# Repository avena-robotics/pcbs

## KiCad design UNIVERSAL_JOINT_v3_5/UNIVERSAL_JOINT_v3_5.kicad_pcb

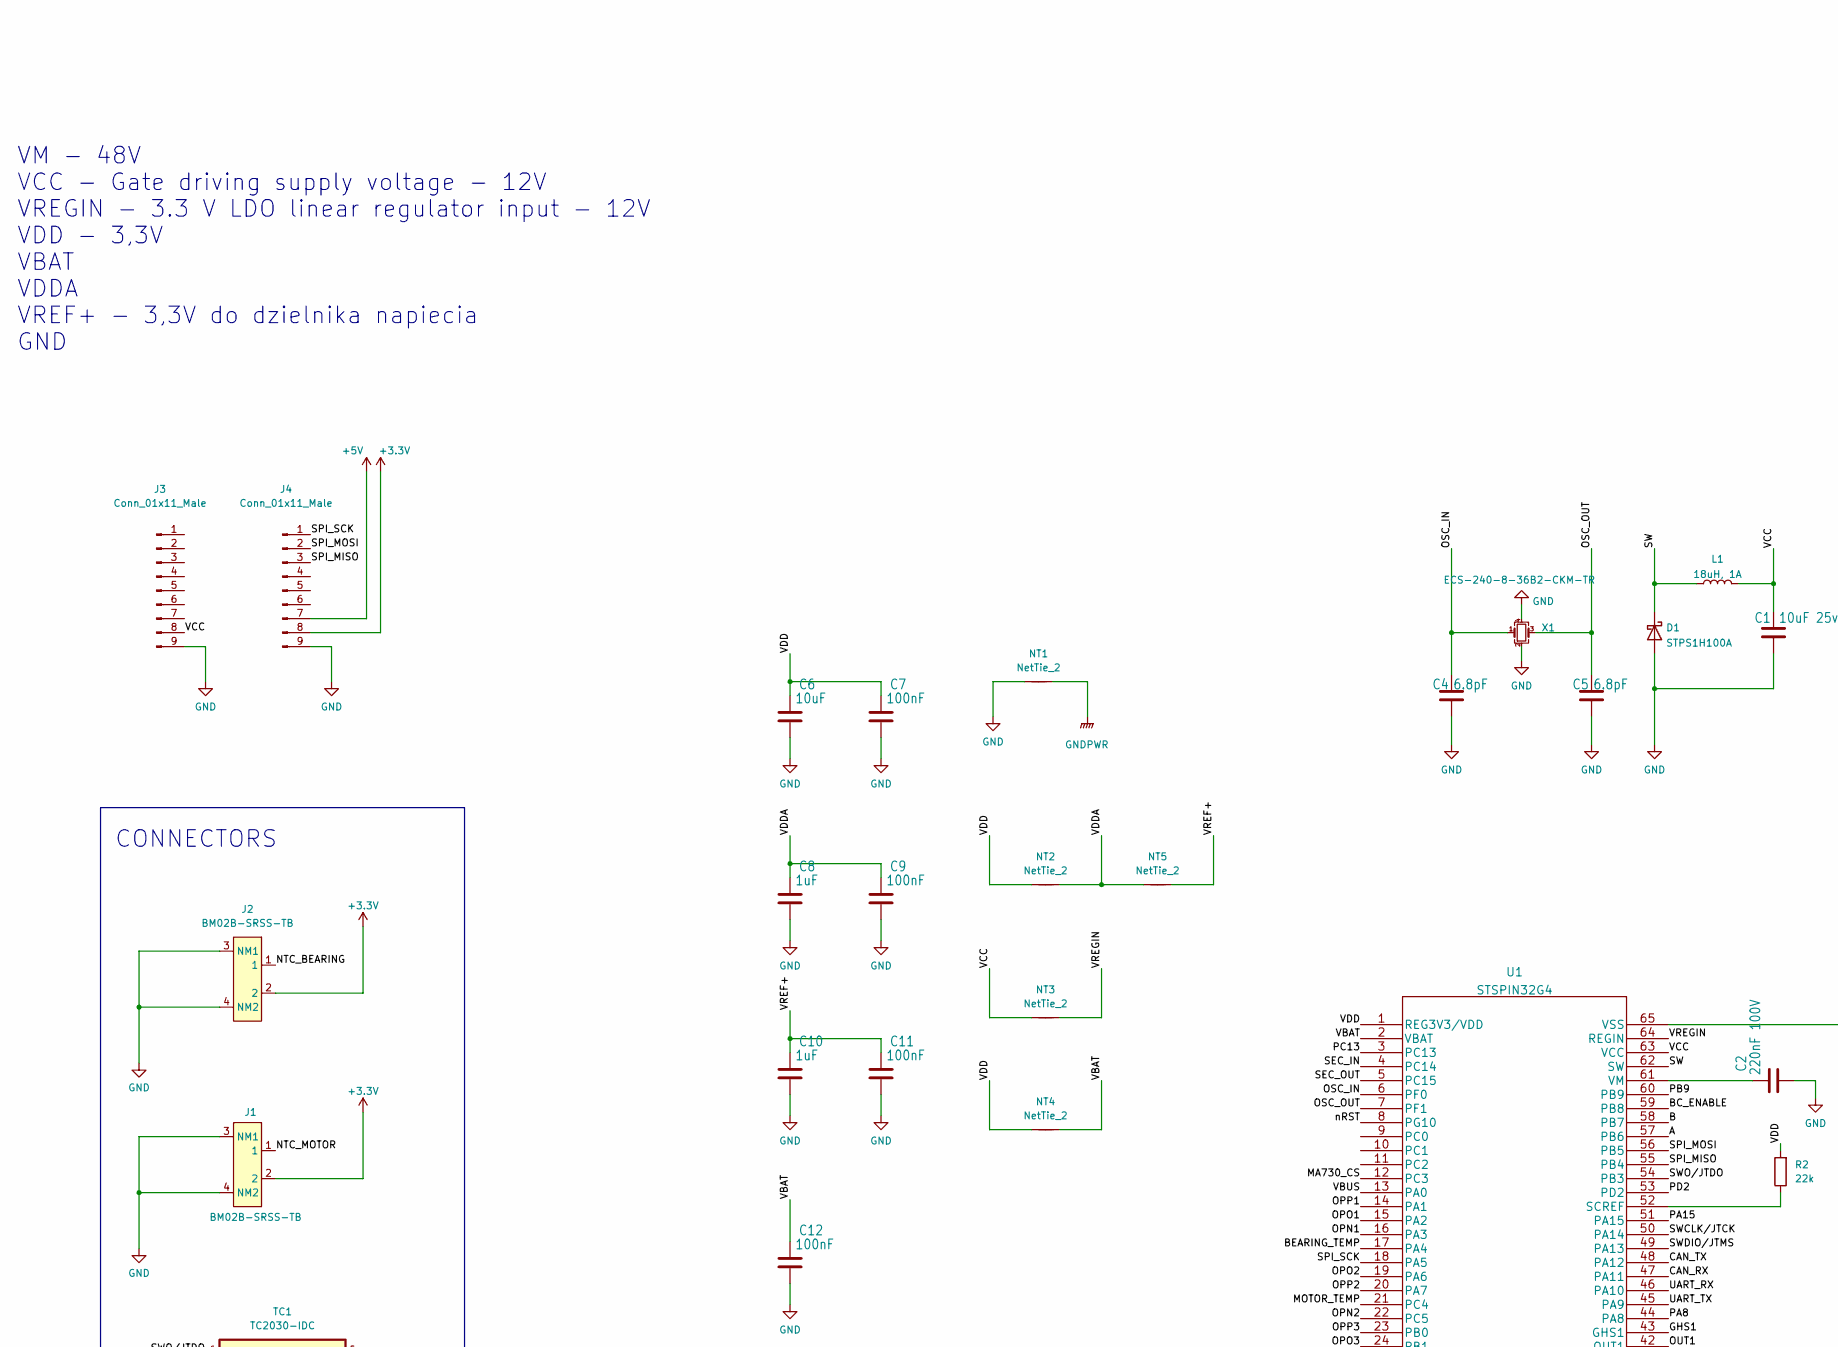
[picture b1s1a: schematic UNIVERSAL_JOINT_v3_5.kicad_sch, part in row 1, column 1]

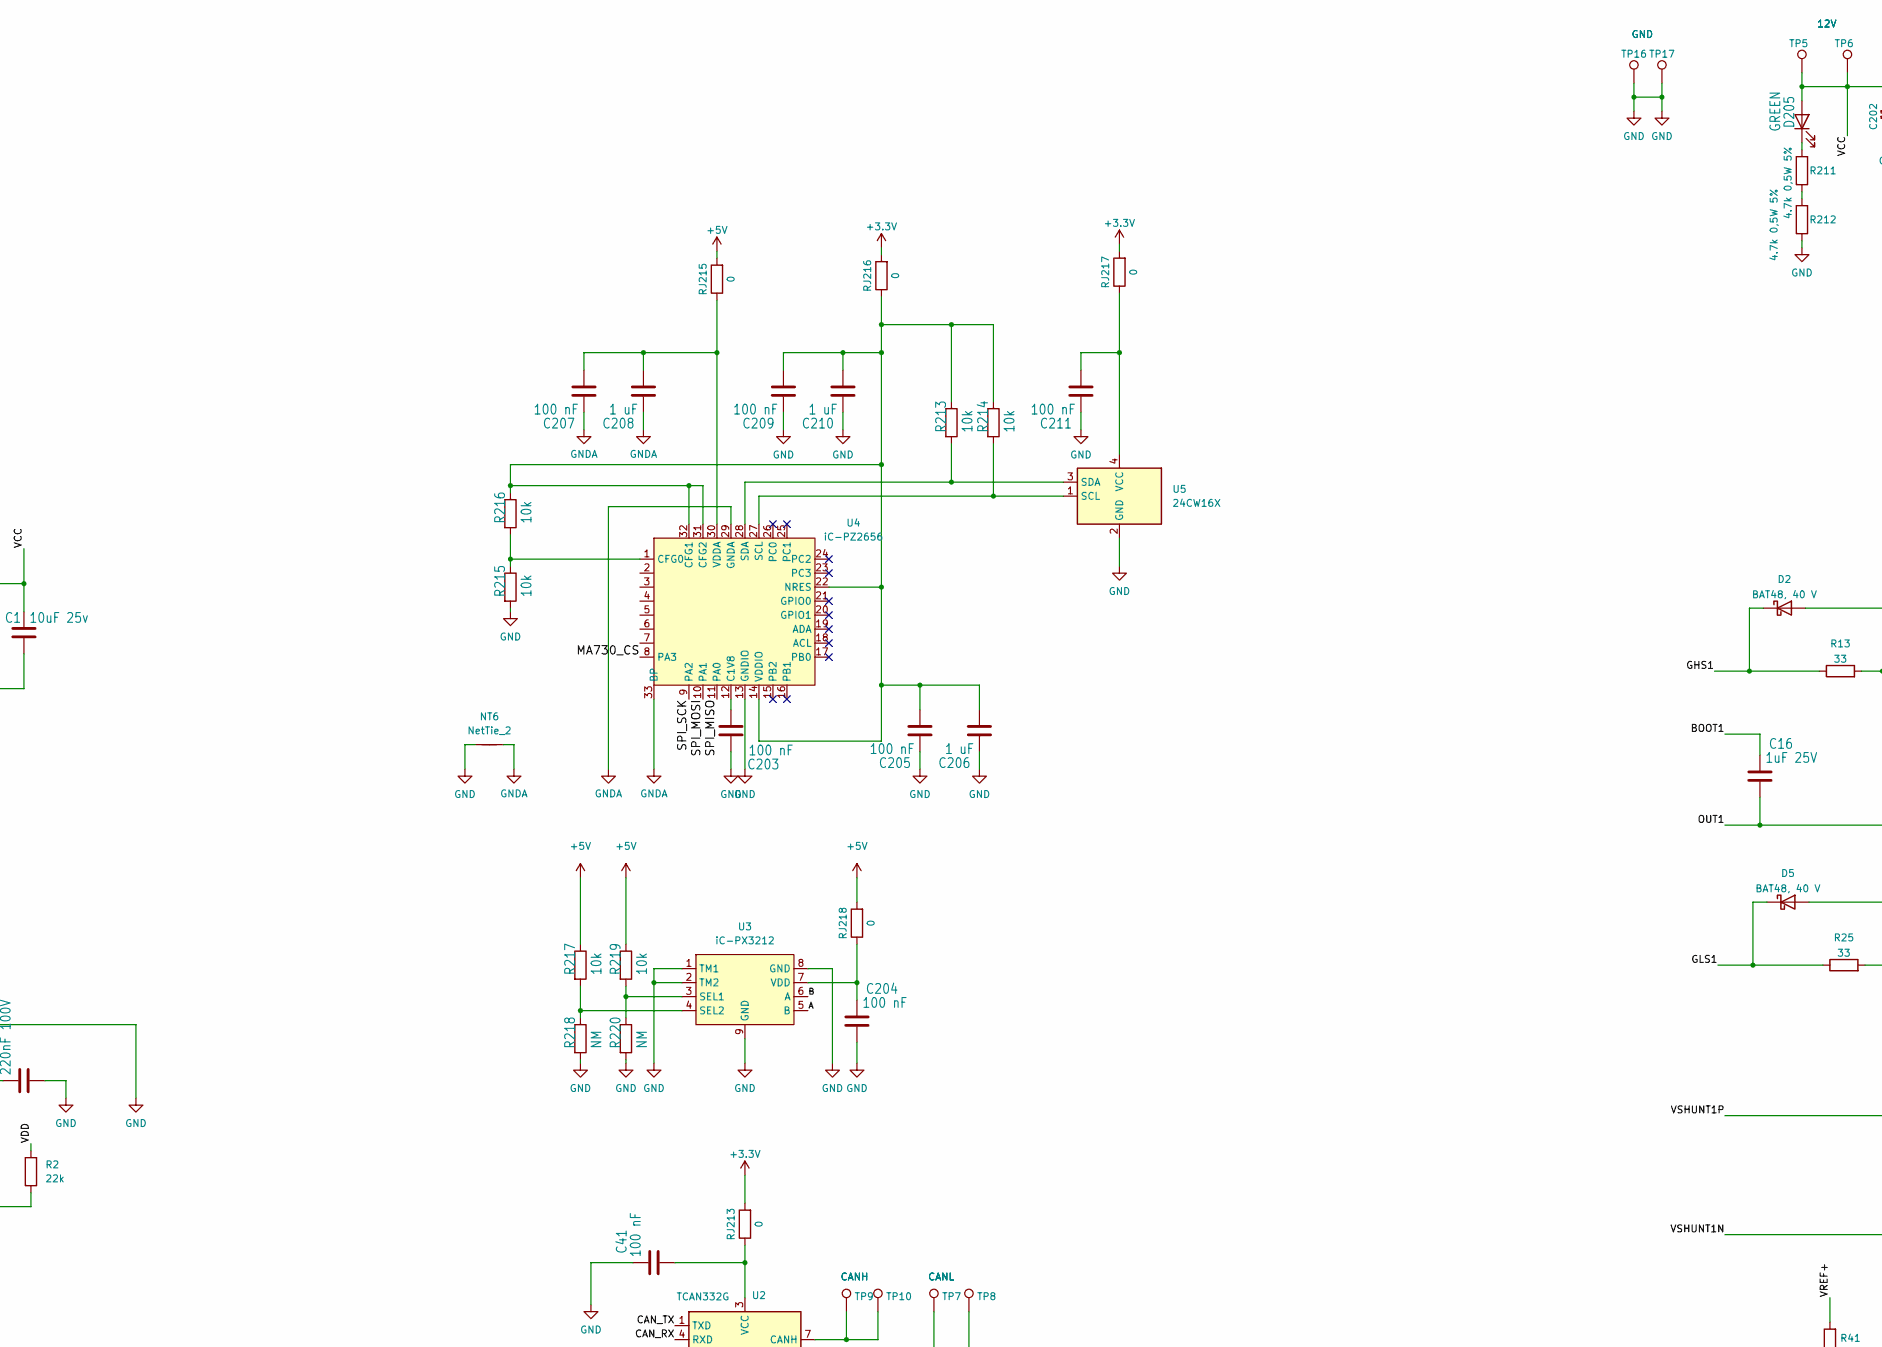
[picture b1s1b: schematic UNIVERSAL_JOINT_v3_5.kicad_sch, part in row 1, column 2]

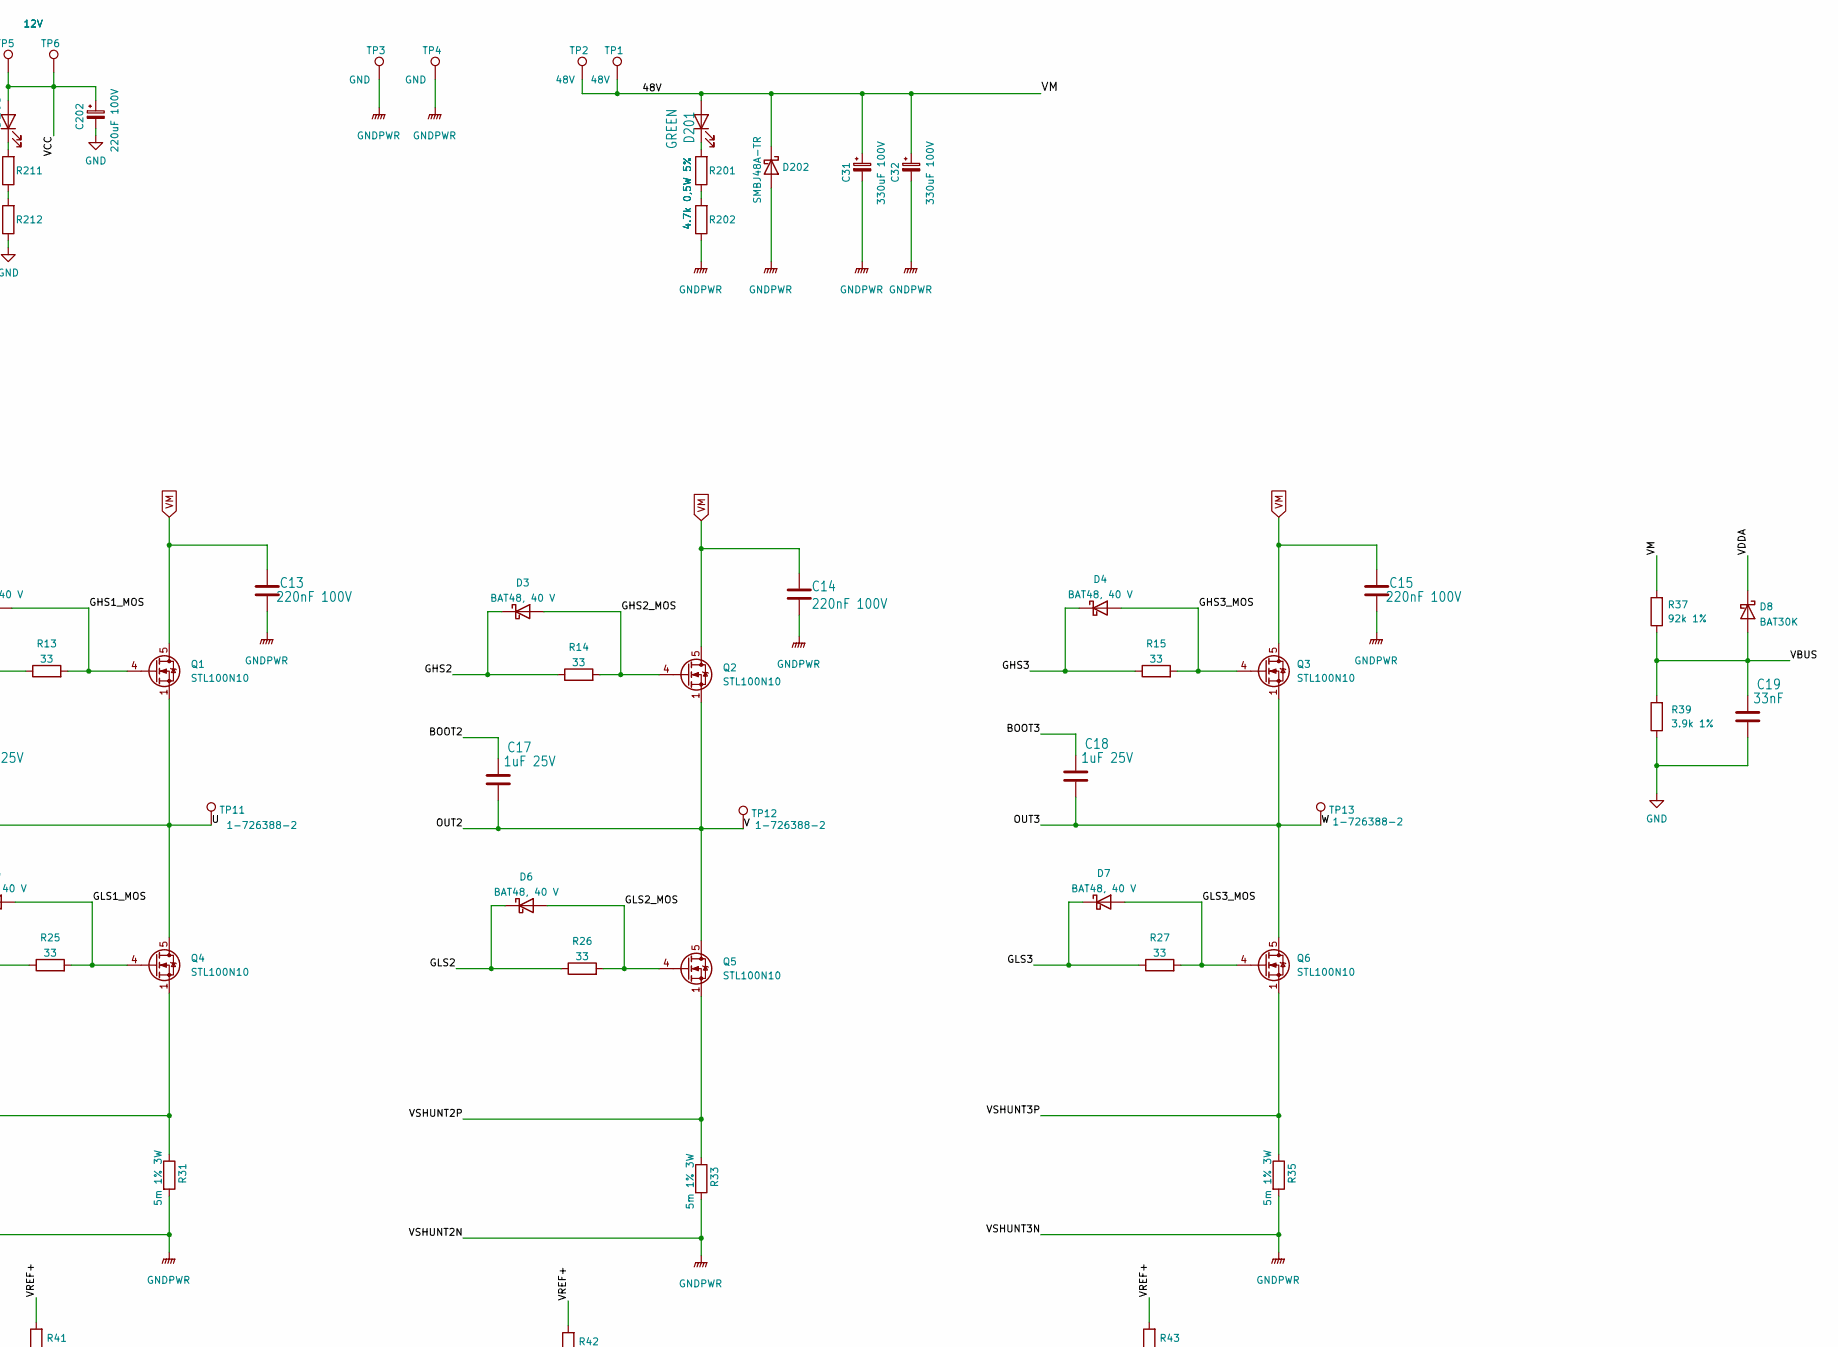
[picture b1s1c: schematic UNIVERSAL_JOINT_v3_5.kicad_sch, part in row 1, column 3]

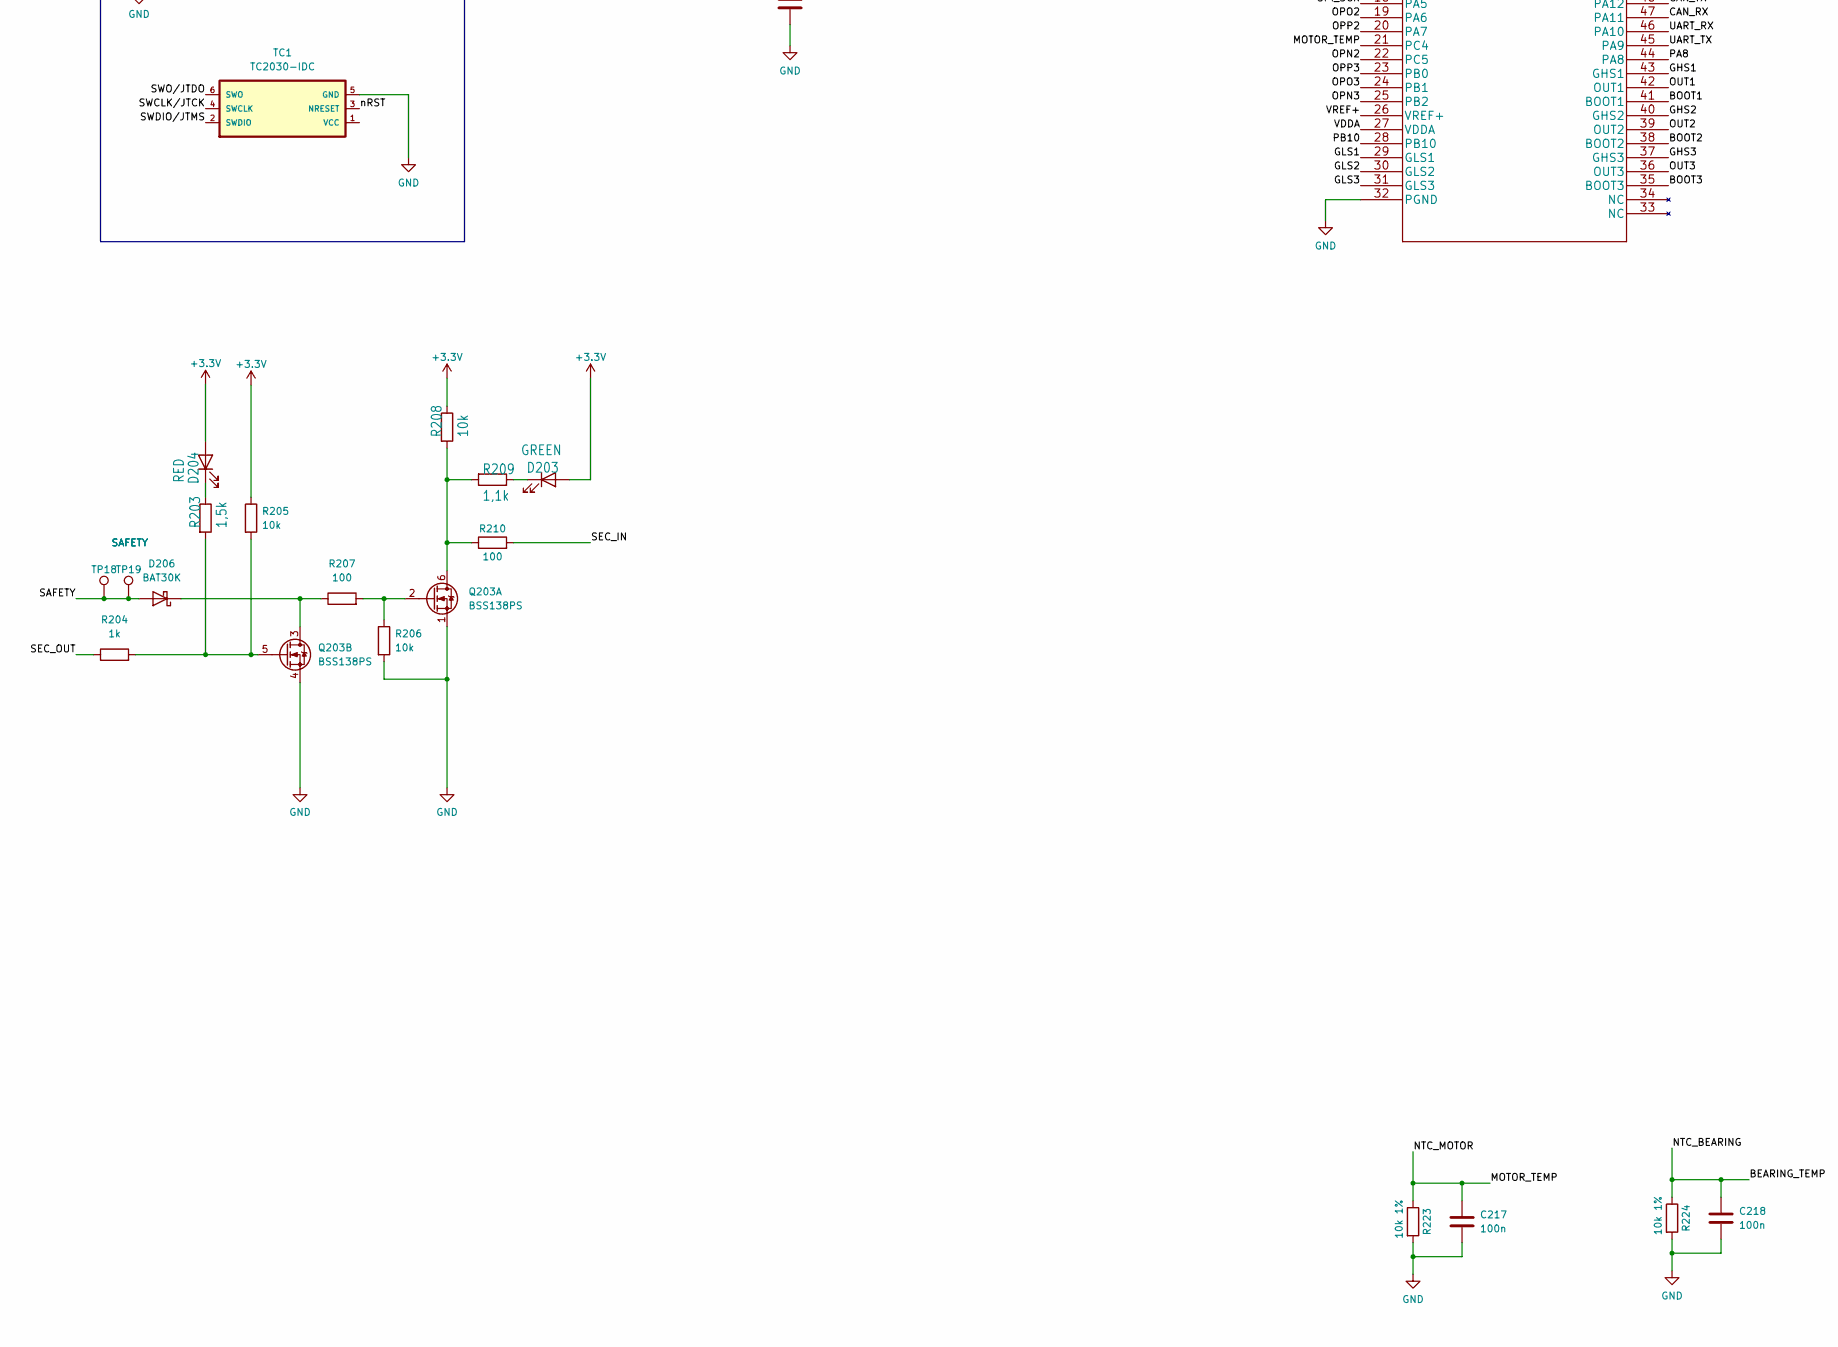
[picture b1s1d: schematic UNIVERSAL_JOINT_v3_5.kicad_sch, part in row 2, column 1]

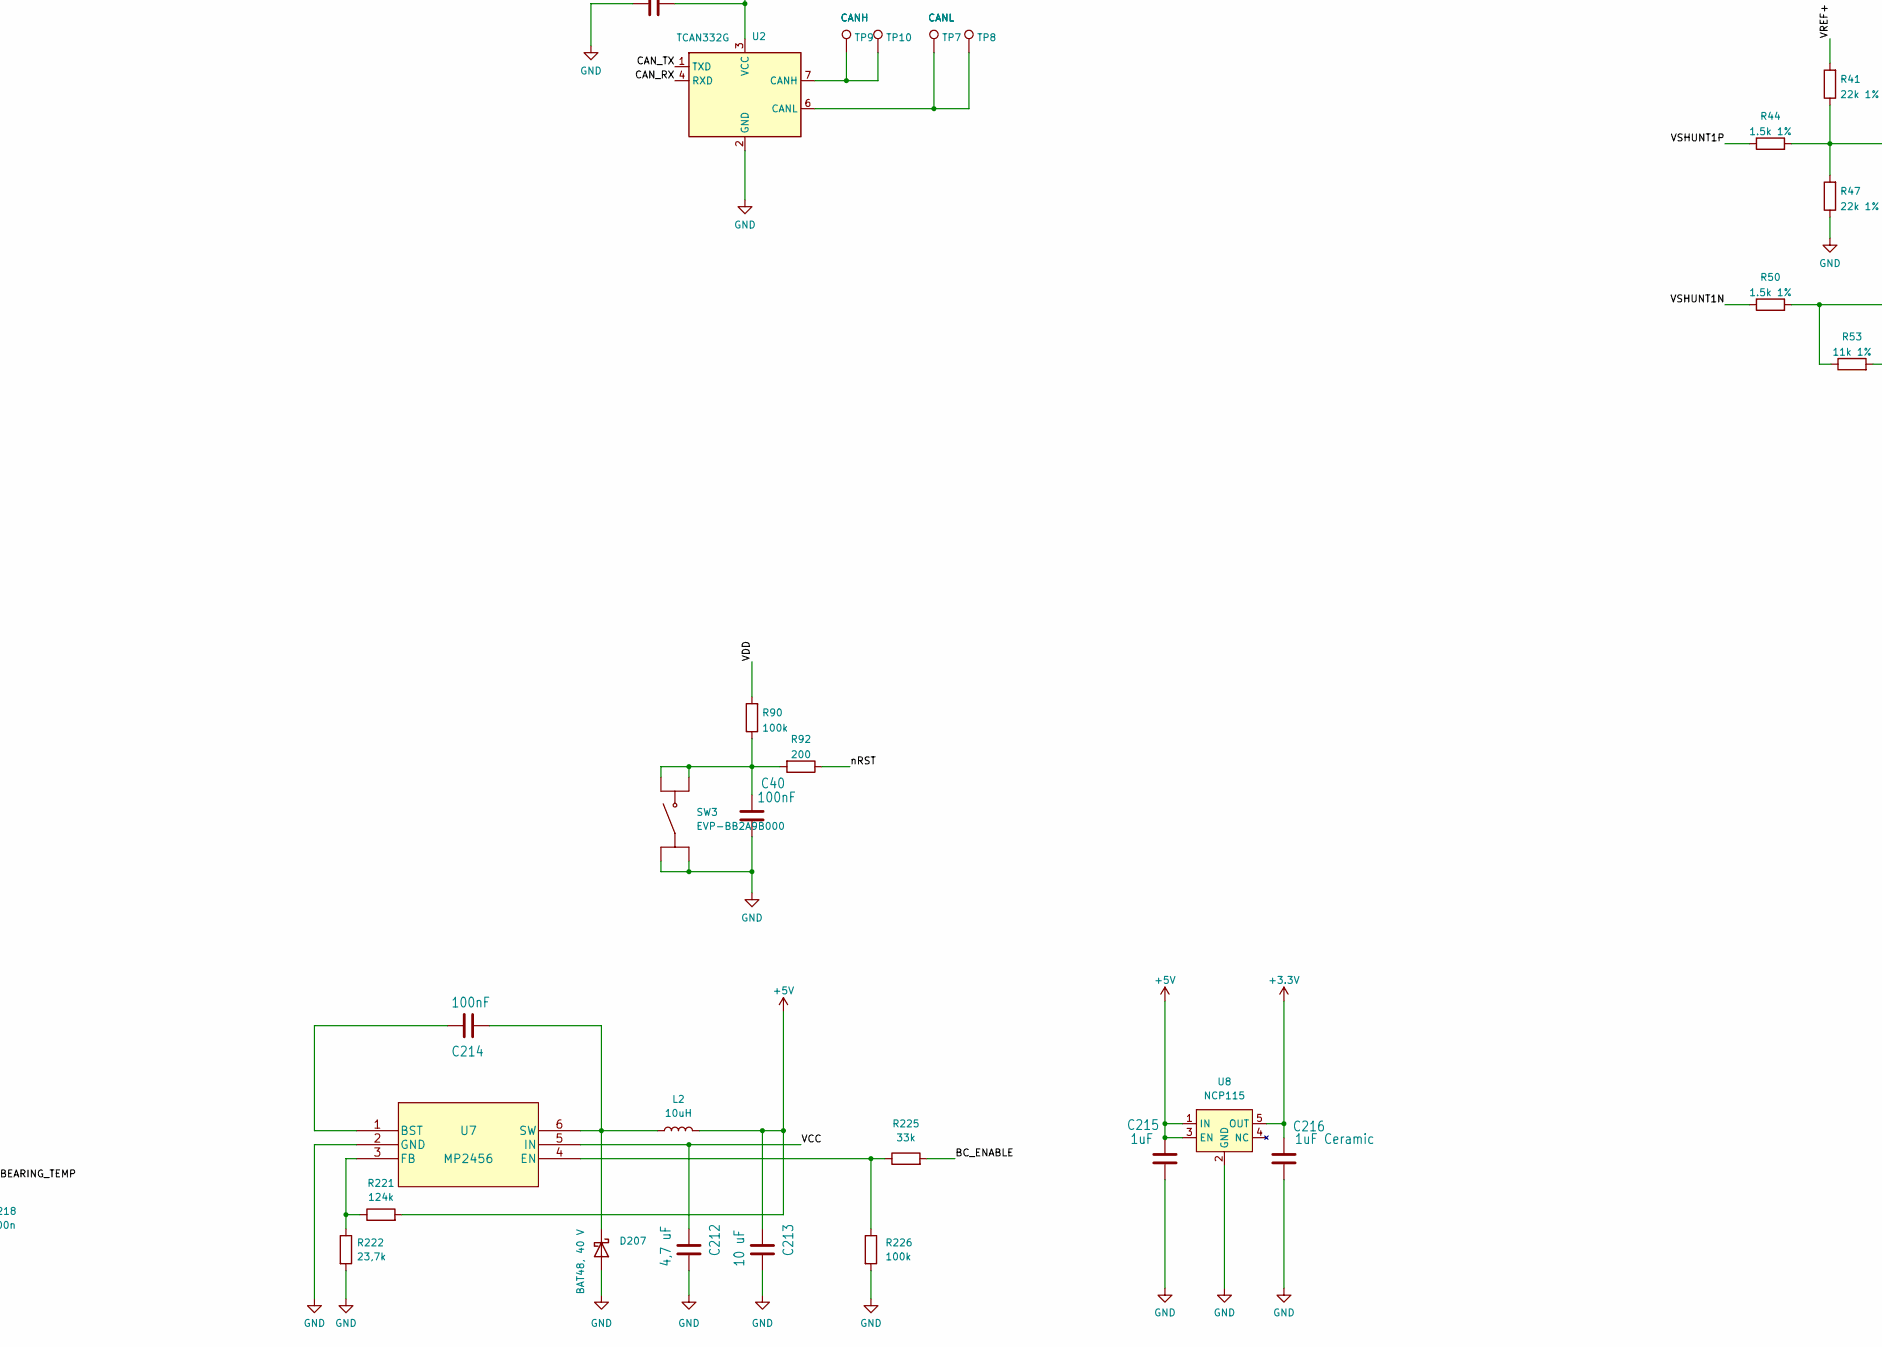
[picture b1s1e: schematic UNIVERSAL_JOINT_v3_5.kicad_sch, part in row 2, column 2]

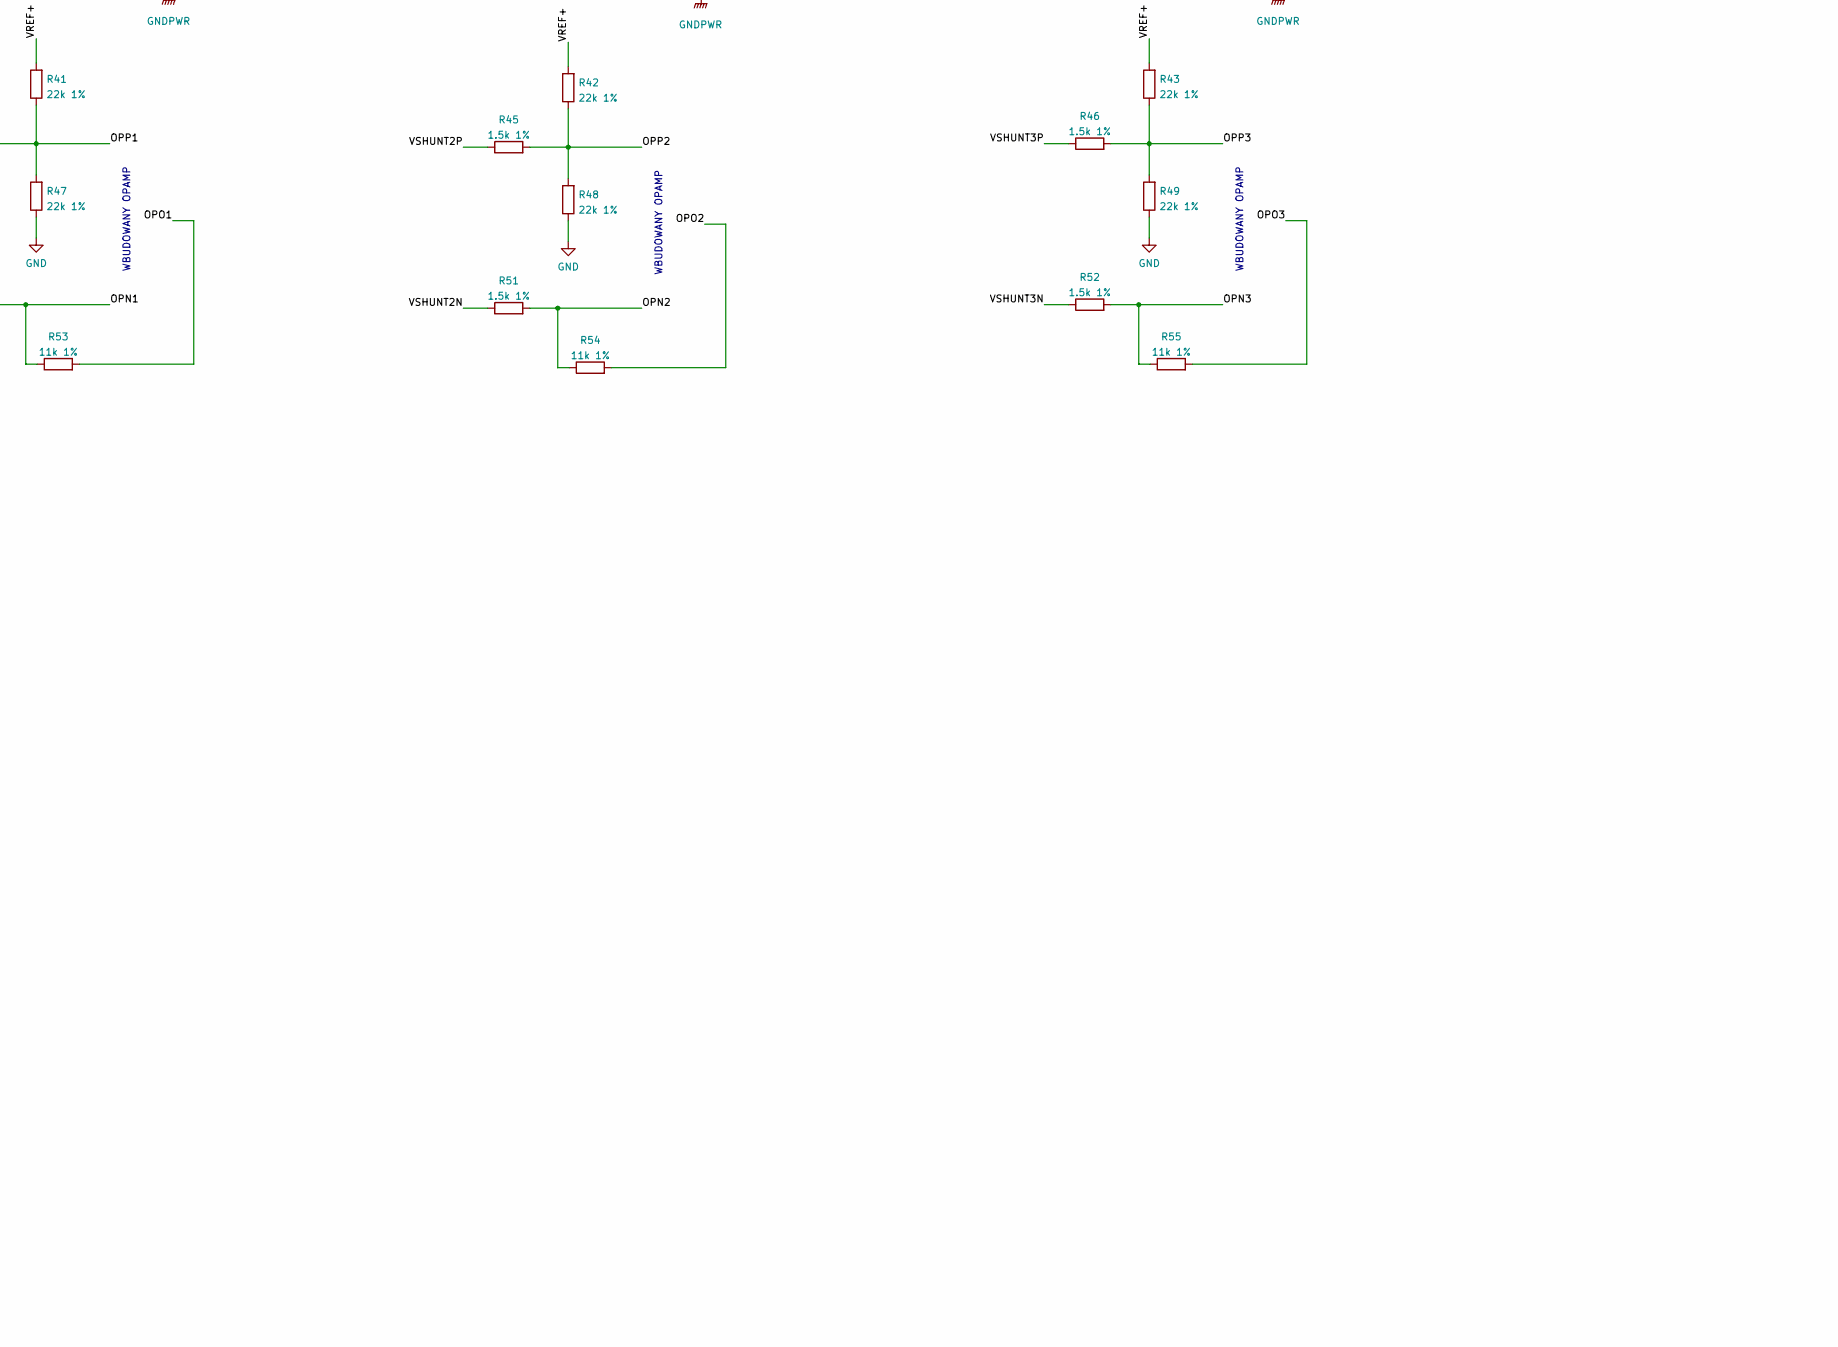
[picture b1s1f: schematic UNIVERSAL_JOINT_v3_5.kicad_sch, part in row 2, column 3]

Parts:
C1: 10uF 25v; C_0805_2012Metric_Pad1.18x1.45mm_HandSolder
C2, C13, C14, C15: 220nF 100V; C_0603_1608Metric_Pad1.08x0.95mm_HandSolder
C4, C5: 6.8pF; C_0603_1608Metric_Pad1.08x0.95mm_HandSolder
C6: 10uF; C_0603_1608Metric_Pad1.08x0.95mm_HandSolder
C7, C9, C11, C12, C40, C214: 100nF; C_0603_1608Metric_Pad1.08x0.95mm_HandSolder
C8, C10, C215: 1uF; C_0603_1608Metric_Pad1.08x0.95mm_HandSolder
C16, C17, C18: 1uF 25V; C_0603_1608Metric_Pad1.08x0.95mm_HandSolder
C19: 33nF; C_0603_1608Metric_Pad1.08x0.95mm_HandSolder
C31, C32: 330uF 100V; CP_Radial_D12.5mm_P5.00mm
C41, C203, C204, C205, C207, C209, C211: 100 nF; C_0603_1608Metric_Pad1.08x0.95mm_HandSolder
C202: 220uF 100V; CP_Radial_D8.0mm_P2.50mm
C206, C208, C210: 1 uF; C_0603_1608Metric_Pad1.08x0.95mm_HandSolder
C212: 4,7 uF; C_0805_2012Metric_Pad1.18x1.45mm_HandSolder
C213: 10 uF; C_0603_1608Metric_Pad1.08x0.95mm_HandSolder
C216: 1uF Ceramic; C_0603_1608Metric_Pad1.08x0.95mm_HandSolder
C217, C218: 100n; C_0603_1608Metric_Pad1.08x0.95mm_HandSolder
D1: STPS1H100A; D_0603_1608Metric_Pad1.05x0.95mm_HandSolder
D2, D3, D4, D5, D6, D7, D207: BAT48, 40 V; D_0603_1608Metric_Pad1.05x0.95mm_HandSolder
D8, D206: BAT30K; D_0603_1608Metric_Pad1.05x0.95mm_HandSolder
D201, D203, D205: GREEN; D_0603_1608Metric_Pad1.05x0.95mm_HandSolder
D202: SMBJ48A-TR; D_SMB
D204: RED; D_0603_1608Metric_Pad1.05x0.95mm_HandSolder
J1, J2: BM02B-SRSS-TB
J3, J4: Conn_01x11_Male; PinHeader_1x09_P1.27mm_Vertical
L1: 18uH, 1A; L_Wuerth_WE-PD2-Typ-MS
L2: 10uH; VLS201612HBX-100M-1
NT1, NT2, NT3, NT4, NT5, NT6: NetTie_2; NetTie-2_SMD_Pad0.5mm
Q1, Q2, Q3, Q4, Q5, Q6: STL100N10; TDSON-8-1
Q203: BSS138PS; SOT363
R2: 22k; R_0402_1005Metric_Pad0.72x0.64mm_HandSolder
R13, R14, R15, R25, R26, R27: 33; R_0402_1005Metric_Pad0.72x0.64mm_HandSolder
R31, R33, R35: 5m 1% 3W; R_2512_6332Metric_Pad1.40x3.35mm_HandSolder
R37: 92k 1%; R_0402_1005Metric_Pad0.72x0.64mm_HandSolder
R39: 3.9k 1%; R_0402_1005Metric_Pad0.72x0.64mm_HandSolder
R41, R42, R43, R47, R48, R49: 22k 1%; R_0402_1005Metric_Pad0.72x0.64mm_HandSolder
R44, R45, R46, R50, R51, R52: 1.5k 1%; R_0402_1005Metric_Pad0.72x0.64mm_HandSolder
R53, R54, R55: 11k 1%; R_0402_1005Metric_Pad0.72x0.64mm_HandSolder
R90, R226: 100k; R_0402_1005Metric_Pad0.72x0.64mm_HandSolder
R92: 200; R_0402_1005Metric_Pad0.72x0.64mm_HandSolder
R201, R202, R211, R212: 4.7k 0,5W 5%; R_0603_1608Metric_Pad0.98x0.95mm_HandSolder
R203: 1,5k; R_0402_1005Metric_Pad0.72x0.64mm_HandSolder
R204: 1k; R_0402_1005Metric_Pad0.72x0.64mm_HandSolder
R205, R206, R208, R213, R214, R215, R216, R217, R219: 10k; R_0402_1005Metric_Pad0.72x0.64mm_HandSolder
R207, R210: 100; R_0402_1005Metric_Pad0.72x0.64mm_HandSolder
R209: 1,1k; R_0402_1005Metric_Pad0.72x0.64mm_HandSolder
R218, R220: NM; R_0402_1005Metric_Pad0.72x0.64mm_HandSolder
R221: 124k; R_0402_1005Metric_Pad0.72x0.64mm_HandSolder
R222: 23,7k; R_0402_1005Metric_Pad0.72x0.64mm_HandSolder
R223, R224: 10k 1%; R_0402_1005Metric_Pad0.72x0.64mm_HandSolder
R225: 33k; R_0402_1005Metric_Pad0.72x0.64mm_HandSolder
RJ213, RJ215, RJ216, RJ217, RJ218: 0; R_0402_1005Metric_Pad0.72x0.64mm_HandSolder
SW3: EVP-BB2A9B000; SW_EVP-BB2A9B000; DIGI-KEY_PART_NUMBER P19888CT-ND
TC1: TC2030-IDC
TP1, TP2: 48V; 1-726388-2
TP3, TP4: GND; 1-726388-2
TP5, TP6: 12V; 61-2348-11_0030
TP7, TP8: CANL; KEYS_3544
TP9, TP10: CANH; 61-2348-11_0030
TP11, TP12, TP13: 1-726388-2; 61-2348-11_0030
TP16, TP17: GND; 61-2348-11_0030
TP18, TP19: SAFETY; KEYS_3544
U1: STSPIN32G4
U2: TCAN332G; SO-8_3.9x4.9mm_P1.27mm
U3: iC-PX3212; oDFN8-3x3
U4: iC-PZ2656; oQFN32-5x5
U5: 24CW16X; SOT-23-5
U7: MP2456; MP2456GJ-Z
U8: NCP115; TSOP-5_1.65x3.05mm_P0.95mm
X1: ECS-240-8-36B2-CKM-TR; Crystal_SMD_2520-4Pin_2.5x2.0mm

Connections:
+3V3: C216.2, D203.2 (A), D204.2 (A), J1.2, J2.2, J4.8, R205.1, R208.1, RJ213.2, RJ216.2, RJ217.2, U8.5 (OUT)
+5V: C213.2, C215.2, J4.7, L2.2, R217.1, R219.1, R221.2, RJ215.2, RJ218.2, U8.1 (IN), U8.3 (EN)
/A: U1.57 (PB6), U3.5 (B)
/B: U1.58 (PB7), U3.6 (A)
/BC_ENABLE: R225.2, U1.59 (PB8)
/BEARING_TEMP: C218.1, J2.1, R224.1, U1.17 (PA4)
/BOOT1: C16.2, U1.41 (BOOT1)
/BOOT2: C17.2, U1.38 (BOOT2)
/BOOT3: C18.2, U1.35 (BOOT3)
/CAN_RX: U1.47 (PA11), U2.4 (RXD)
/CAN_TX: U1.48 (PA12), U2.1 (TXD)
/GHS1: D2.1 (K), R13.1, U1.43 (GHS1)
/GHS1_MOS: D2.2 (A), Q1.4 (G), R13.2
/GHS2: D3.1 (K), R14.1, U1.40 (GHS2)
/GHS2_MOS: D3.2 (A), Q2.4 (G), R14.2
/GHS3: D4.1 (K), R15.1, U1.37 (GHS3)
/GHS3_MOS: D4.2 (A), Q3.4 (G), R15.2
/GLS1: D5.1 (K), R25.1, U1.29 (GLS1)
/GLS1_MOS: D5.2 (A), Q4.4 (G), R25.2
/GLS2: D6.1 (K), R26.1, U1.30 (GLS2)
/GLS2_MOS: D6.2 (A), Q5.4 (G), R26.2
/GLS3: D7.1 (K), R27.1, U1.31 (GLS3)
/GLS3_MOS: D7.2 (A), Q6.4 (G), R27.2
/MA730_CS: U1.12 (PC3), U4.8 (PA3)
/MOTOR_TEMP: C217.1, J1.1, R223.1, U1.21 (PC4)
/OPN1: R50.2, R53.1, U1.16 (PA3)
/OPN2: R51.2, R54.1, U1.22 (PC5)
/OPN3: R52.2, R55.1, U1.25 (PB2)
/OPO1: R53.2, U1.15 (PA2)
/OPO2: R54.2, U1.19 (PA6)
/OPO3: R55.2, U1.24 (PB1)
/OPP1: R41.1, R44.2, R47.2, U1.14 (PA1)
/OPP2: R42.1, R45.2, R48.2, U1.20 (PA7)
/OPP3: R43.1, R46.2, R49.2, U1.23 (PB0)
/OSC_IN: C4.2, U1.6 (PF0), X1.1
/OSC_OUT: C5.2, U1.7 (PF1), X1.3
/OUT1: C16.1, Q1.1 (S), Q1.2 (S), Q1.3 (S), Q4.5 (D), TP11.1, U1.42 (OUT1)
/OUT2: C17.1, Q2.1 (S), Q2.2 (S), Q2.3 (S), Q5.5 (D), TP12.1, U1.39 (OUT2)
/OUT3: C18.1, Q3.1 (S), Q3.2 (S), Q3.3 (S), Q6.5 (D), TP13.1, U1.36 (OUT3)
/PA8: U1.44 (PA8)
/PA15: U1.51 (PA15)
/PB9: U1.60 (PB9)
/PB10: U1.28 (PB10)
/PC13: U1.3 (PC13)
/PD2: U1.53 (PD2)
/SAFETY: D206.2 (A), TP18.1, TP19.1
/SEC_IN: R210.2, U1.4 (PC14)
/SEC_OUT: R204.1, U1.5 (PC15)
/SPI_MISO: J4.3, U1.55 (PB4), U4.11 (PA0)
/SPI_MOSI: J4.2, U1.56 (PB5), U4.10 (PA1)
/SPI_SCK: J4.1, U1.18 (PA5), U4.9 (PA2)
/SW: D1.1 (K), L1.1, U1.62 (SW)
/SWCLK/JTCK: TC1.4 (SWCLK), U1.50 (PA14)
/SWDIO/JTMS: TC1.2 (SWDIO), U1.49 (PA13)
/SWO/JTDO: TC1.6 (SWO), U1.54 (PB3)
/UART_RX: U1.46 (PA10)
/UART_TX: U1.45 (PA9)
/VBAT: C12.2, NT4.2, U1.2 (VBAT)
/VBUS: C19.2, D8.2 (A), R37.1, R39.2, U1.13 (PA0)
/VCC: C1.2, C202.1, C212.2, D205.2 (A), J3.8, L1.2, NT3.1, TP5.1, TP6.1, U1.63 (VCC), U7.5 (IN)
/VDD: C6.2, C7.2, NT2.1, NT4.1, R2.2, R90.2, U1.1 (REG3V3/VDD)
/VDDA: C8.2, C9.2, D8.1 (K), NT2.2, NT5.1, U1.27 (VDDA)
/VREF+: C10.2, C11.2, NT5.2, R41.2, R42.2, R43.2, U1.26 (VREF+)
/VREGIN: NT3.2, U1.64 (REGIN)
/VSHUNT1P: Q4.1 (S), Q4.2 (S), Q4.3 (S), R31.1, R44.1
/VSHUNT2P: Q5.1 (S), Q5.2 (S), Q5.3 (S), R33.1, R45.1
/VSHUNT3P: Q6.1 (S), Q6.2 (S), Q6.3 (S), R35.1, R46.1
/nRST: R92.1, TC1.3 (NRESET), U1.8 (PG10)
GND: C1.1, C2.1, C4.1, C5.1, C6.1, C7.1, C8.1, C9.1, C10.1, C11.1, C12.1, C19.1, C40.1, C41.2, C202.2, C203.2, C204.1, C205.2, C206.2, C209.2, C210.2, C211.2, C212.1, C213.1, C215.1, C216.1, C217.2, C218.2, D1.2 (A), D207.2 (A), J1.3 (NM1), J1.4 (NM2), J2.3 (NM1), J2.4 (NM2), J3.9, J4.9, NT1.1, NT6.1, Q203.1 (S1), Q203.4 (S2), R39.1, R47.1, R48.1, R49.1, R206.2, R212.1, R215.2, R218.2, R220.2, R222.2, R223.2, R224.2, R226.2, SW3.A1, SW3.A2, TC1.5 (GND), TP16.1, TP17.1, U1.32 (PGND), U1.65 (VSS), U2.2 (GND), U3.1 (TM1), U3.2 (TM2), U3.8 (GND), U3.9 (GND), U4.13 (GNDIO), U5.2 (GND), U7.2 (GND), U8.2 (GND), X1.2, X1.4
GNDA: C207.2, C208.2, NT6.2, U4.29 (GNDA), U4.33 (BP)
GNDPWR: C13.1, C14.1, C15.1, C31.2, C32.2, D202.2 (A), NT1.2, R31.2, R33.2, R35.2, R50.1, R51.1, R52.1, R202.1, TP3.1, TP4.1
unnamed: C2.2, U1.61 (VM)
unnamed: C40.2, R90.1, R92.2, SW3.B1, SW3.B2
unnamed: C41.1, RJ213.1, U2.3 (VCC)
unnamed: C203.1, U4.12 (C1V8)
unnamed: C204.2, RJ218.1, U3.7 (VDD)
unnamed: C205.1, C206.1, C209.1, C210.1, R213.1, R214.1, R216.1, RJ216.1, U4.14 (VDDIO), U4.22 (NRES), U4.31 (CFG2), U4.32 (CFG1)
unnamed: C207.1, C208.1, RJ215.1, U4.30 (VDDA)
unnamed: C211.1, RJ217.1, U5.4 (VCC)
unnamed: C214.1, U7.1 (BST)
unnamed: C214.2, D207.1 (K), L2.1, U7.6 (SW)
unnamed: D201.1 (K), R201.2
unnamed: D203.1 (K), R209.1
unnamed: D204.1 (K), R203.1
unnamed: D205.1 (K), R211.2
unnamed: D206.1 (K), Q203.3 (D2), R207.1
unnamed: Q203.2 (G1), R206.1, R207.2
unnamed: Q203.5 (G2), R203.2, R204.2, R205.2
unnamed: Q203.6 (D1), R208.2, R209.2, R210.1
unnamed: R2.1, U1.52 (SCREF)
unnamed: R201.1, R202.2
unnamed: R211.1, R212.2
unnamed: R213.2, U4.28 (SDA), U5.3 (SDA)
unnamed: R214.2, U4.27 (SCL), U5.1 (SCL)
unnamed: R215.1, R216.2, U4.1 (CFG0)
unnamed: R217.2, R218.1, U3.4 (SEL2)
unnamed: R219.2, R220.1, U3.3 (SEL1)
unnamed: R221.1, R222.1, U7.3 (FB)
unnamed: R225.1, R226.1, U7.4 (EN)
unnamed: TP7.1, TP8.1, U2.6 (CANL)
unnamed: TP9.1, TP10.1, U2.7 (CANH)
VM: C13.2, C14.2, C15.2, C31.1, C32.1, D201.2 (A), D202.1 (K), Q1.5 (D), Q2.5 (D), Q3.5 (D), R37.2, TP1.1, TP2.1

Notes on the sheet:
VM - 48V VCC - Gate driving supply voltage - 12V VREGIN - 3.3 V LDO linear regulator input - 12V VDD - 3,3V VBAT VDDA VREF+ - 3,3V do dzielnika napiecia GND
CONNECTORS
WBUDOWANY OPAMP

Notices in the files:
parts and their libraries:
Copyright 2021 Accelerated Designs. All rights reserved.
